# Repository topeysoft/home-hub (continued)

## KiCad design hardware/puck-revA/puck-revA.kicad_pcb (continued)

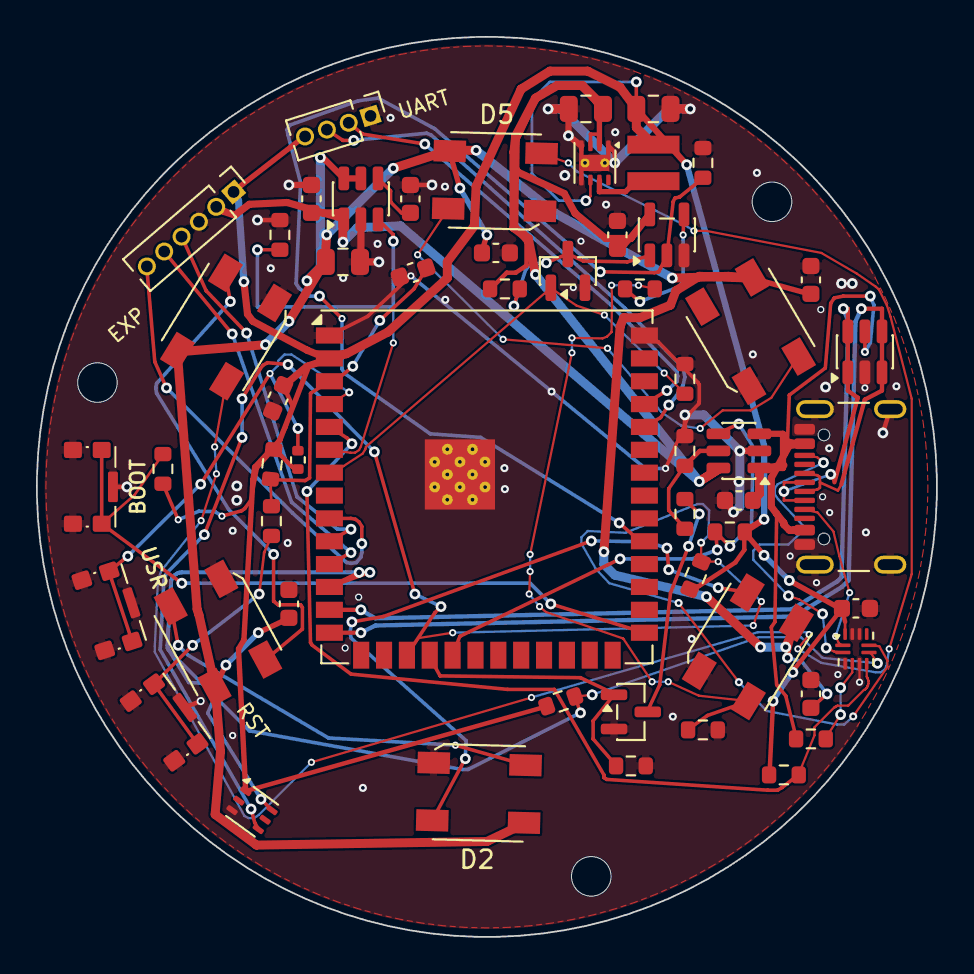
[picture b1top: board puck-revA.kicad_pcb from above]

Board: 4 copper layers, 50.0 x 50.0 mm, 58 parts (0 on the bottom side), 39 nets.

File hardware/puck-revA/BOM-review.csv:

Reference,Value,Footprint,Manufacturer,MPN,LCSC,Assembly,Sourcing_Status
C1,22u 25V X5R,Capacitor_SMD:C_0805_2012Metric,Murata,GRM21BR61E226ME44L,C86816,SMD candidate,
C2,22u 25V X5R,Capacitor_SMD:C_0805_2012Metric,Murata,GRM21BR61E226ME44L,C86816,SMD candidate,
C3,10u 16V X5R,Capacitor_SMD:C_0603_1608Metric,Murata,GRM188R61C106KAALD,C86275,SMD candidate,
C7,10u 16V X5R,Capacitor_SMD:C_0603_1608Metric,Murata,GRM188R61C106KAALD,C86275,SMD candidate,
C8,100n 50V X7R,Capacitor_SMD:C_0603_1608Metric,Samsung Electro-Mechanics,CL10B104KB8NNNC,C1591,SMD candidate,
C9,10u 25V X5R,Capacitor_SMD:C_0805_2012Metric,Samsung Electro-Mechanics,CL21A106KAYNNNE,C15850,SMD candidate,
C10,1n 50V C0G,Capacitor_SMD:C_0603_1608Metric,Samsung Electro-Mechanics,CL10C102JB8NNNC,C163508,SMD candidate,
C11,1u 25V X7R,Capacitor_SMD:C_0603_1608Metric,Samsung Electro-Mechanics,CL10B105KA8NNNC,C29936,SMD candidate,
C12,100n 50V X7R,Capacitor_SMD:C_0603_1608Metric,Samsung Electro-Mechanics,CL10B104KB8NNNC,C1591,SMD candidate,
C13,1u 25V X7R,Capacitor_SMD:C_0603_1608Metric,Samsung Electro-Mechanics,CL10B105KA8NNNC,C29936,SMD candidate,
C101,100n 50V X7R,Capacitor_SMD:C_0603_1608Metric,Samsung Electro-Mechanics,CL10B104KB8NNNC,C1591,SMD candidate,
C102,100n 50V X7R,Capacitor_SMD:C_0603_1608Metric,Samsung Electro-Mechanics,CL10B104KB8NNNC,C1591,SMD candidate,
C103,100n 50V X7R,Capacitor_SMD:C_0603_1608Metric,Samsung Electro-Mechanics,CL10B104KB8NNNC,C1591,SMD candidate,
C104,100n 50V X7R,Capacitor_SMD:C_0603_1608Metric,Samsung Electro-Mechanics,CL10B104KB8NNNC,C1591,SMD candidate,
D1,SKC6812RGBW-WS-000,Puck:LED_SKC6812RGBW_WS_5050,OPSCO,SKC6812RGBW-WS-000,C5378724,SMD candidate,
D2,SKC6812RGBW-WS-000,Puck:LED_SKC6812RGBW_WS_5050,OPSCO,SKC6812RGBW-WS-000,C5378724,SMD candidate,
D3,SKC6812RGBW-WS-000,Puck:LED_SKC6812RGBW_WS_5050,OPSCO,SKC6812RGBW-WS-000,C5378724,SMD candidate,
D4,SKC6812RGBW-WS-000,Puck:LED_SKC6812RGBW_WS_5050,OPSCO,SKC6812RGBW-WS-000,C5378724,SMD candidate,
D5,SKC6812RGBW-WS-000,Puck:LED_SKC6812RGBW_WS_5050,OPSCO,SKC6812RGBW-WS-000,C5378724,SMD candidate,
D6,SKC6812RGBW-WS-000,Puck:LED_SKC6812RGBW_WS_5050,OPSCO,SKC6812RGBW-WS-000,C5378724,SMD candidate,
H1,M2,MountingHole:MountingHole_2.2mm_M2,,,,Mechanical,
H2,M2,MountingHole:MountingHole_2.2mm_M2,,,,Mechanical,
H3,M2,MountingHole:MountingHole_2.2mm_M2,,,,Mechanical,
J1,USB-C 16P,Connector_USB:USB_C_Receptacle_GCT_USB4105-xx-A_16P_TopMnt_Horizontal,Global Connector Technology,USB4105-GF-A-120,C5184243,SMD candidate,
J2,UART,Connector_PinHeader_1.27mm:PinHeader_1x04_P1.27mm_Vertical,,,,Optional manual header,
J3,EXP (DNP on the product),Connector_PinHeader_1.27mm:PinHeader_1x06_P1.27mm_Vertical,,,,DNP,
L1,XFL3012-222MEC 2.2uH,Puck:L_Coilcraft_XFL3012,Coilcraft,XFL3012-222MEC,C3911432,SMD candidate,
Q1,AO3400A,Package_TO_SOT_SMD:SOT-23,Alpha & Omega Semiconductor,AO3400A,C20917,SMD candidate,
Q2,AO3400A,Package_TO_SOT_SMD:SOT-23,Alpha & Omega Semiconductor,AO3400A,C20917,SMD candidate,
R3,2k2,Resistor_SMD:R_0603_1608Metric,UNI-ROYAL,0603WAF2201T5E,C4190,SMD candidate,
R4,300,Resistor_SMD:R_0603_1608Metric,UNI-ROYAL,0603WAF3000T5E,C23025,SMD candidate,
R5,4k7,Resistor_SMD:R_0603_1608Metric,UNI-ROYAL,0603WAF4701T5E,C23162,SMD candidate,
R6,4k7,Resistor_SMD:R_0603_1608Metric,UNI-ROYAL,0603WAF4701T5E,C23162,SMD candidate,
R7,2k2,Resistor_SMD:R_0402_1005Metric,UNI-ROYAL,0402WGF2201TCE,C25879,SMD candidate,
R8,887k 1%,Resistor_SMD:R_0603_1608Metric,YAGEO,RC0603FR-07887KL,C246015,SMD candidate,
R9,200k,Resistor_SMD:R_0603_1608Metric,UNI-ROYAL,0603WAF2003T5E,C25811,SMD candidate,
R10,10k,Resistor_SMD:R_0603_1608Metric,UNI-ROYAL,0603WAF1002T5E,C25804,SMD candidate,
R11,10k,Resistor_SMD:R_0603_1608Metric,UNI-ROYAL,0603WAF1002T5E,C25804,SMD candidate,
R12,100k,Resistor_SMD:R_0603_1608Metric,UNI-ROYAL,0603WAF1003T5E,C25803,SMD candidate,
R13,10k,Resistor_SMD:R_0603_1608Metric,UNI-ROYAL,0603WAF1002T5E,C25804,SMD candidate,
R14,100k,Resistor_SMD:R_0603_1608Metric,UNI-ROYAL,0603WAF1003T5E,C25803,SMD candidate,
R15,66k5 1%,Resistor_SMD:R_0603_1608Metric,YAGEO,RC0603FR-0766K5L,C137691,SMD candidate,
R16,32k4 1%,Resistor_SMD:R_0603_1608Metric,UNI-ROYAL,0603WAF3242T5E,C13187,SMD candidate,
R17,100k,Resistor_SMD:R_0603_1608Metric,UNI-ROYAL,0603WAF1003T5E,C25803,SMD candidate,
R18,10k,Resistor_SMD:R_0603_1608Metric,UNI-ROYAL,0603WAF1002T5E,C25804,SMD candidate,
R19,2k2,Resistor_SMD:R_0603_1608Metric,UNI-ROYAL,0603WAF2201T5E,C4190,SMD candidate,
R20,300,Resistor_SMD:R_0603_1608Metric,UNI-ROYAL,0603WAF3000T5E,C23025,SMD candidate,
SW1,KMS221GLFS,Button_Switch_SMD:SW_SPST_CK_KMS2xxG,C&K / Littelfuse,KMS221GLFS,C221698,SMD candidate,JLCPCB C221698; side actuated; no pegs; pull-ups revised for minimum switching current
SW2,KMS221GLFS,Button_Switch_SMD:SW_SPST_CK_KMS2xxG,C&K / Littelfuse,KMS221GLFS,C221698,SMD candidate,JLCPCB C221698; side actuated; no pegs; pull-ups revised for minimum switching current
SW3,KMS221GLFS,Button_Switch_SMD:SW_SPST_CK_KMS2xxG,C&K / Littelfuse,KMS221GLFS,C221698,SMD candidate,JLCPCB C221698; side actuated; no pegs; pull-ups revised for minimum switching current
U1,ESP32-S3-WROOM-1U-N16,RF_Module:ESP32-S3-WROOM-1U,Espressif,ESP32-S3-WROOM-1U-N16,C2980298,SMD candidate,
U2,TPS62162DSGR,Package_SON:Texas_DSG0008A_WSON-8-1EP_2x2mm_P0.5mm_EP0.9x1.6mm_ThermalVias,Texas Instruments,TPS62162DSGR,C40256,SMD candidate,
U3,SN74LV1T125DBVR,Package_TO_SOT_SMD:SOT-23-5,Texas Instruments,SN74LV1T125DBVR,C473338,SMD candidate,
U4,USBLC6-2SC6,Package_TO_SOT_SMD:SOT-23-6,STMicroelectronics,USBLC6-2SC6,C7519,SMD candidate,
U5,"ambient light, DNP",OptoDevice:Lite-On_LTR-303ALS-01,,,,DNP,
U6,TUSB320IRWBR,Package_DFN_QFN:Texas_X2QFN-12_1.6x1.6mm_P0.4mm,Texas Instruments,TUSB320IRWBR,C80170,SMD candidate,
U7,TPS22918DBVR,Package_TO_SOT_SMD:SOT-23-6,Texas Instruments,TPS22918DBVR,C131941,SMD candidate,
U8,TPS2553DBVR,Package_TO_SOT_SMD:SOT-23-6,Texas Instruments,TPS2553DBVR,C55266,SMD candidate,
